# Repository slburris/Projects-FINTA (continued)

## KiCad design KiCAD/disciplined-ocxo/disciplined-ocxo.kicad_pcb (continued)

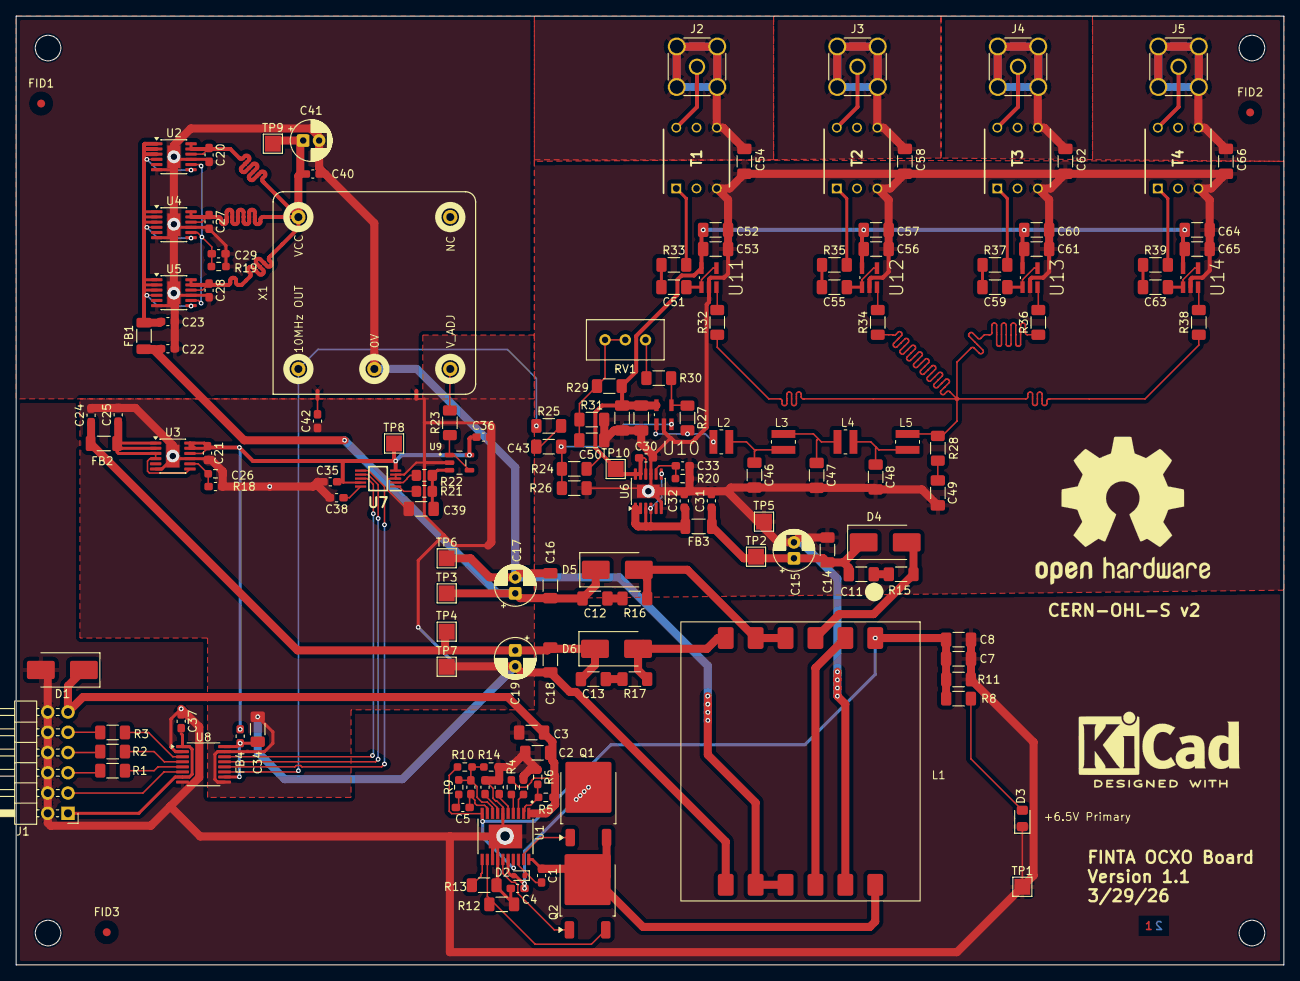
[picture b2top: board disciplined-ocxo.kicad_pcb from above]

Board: 2 copper layers, 159.0 x 119.0 mm, 166 parts (0 on the bottom side), 96 nets.

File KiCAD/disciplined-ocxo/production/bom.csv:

Designator,Footprint,Quantity,Value,LCSC Part #
C1,0603,1,100nf,
C10,0603,1,150pf,
"C11, C12, C13",1206,3,C,
"C14, C16, C18",1206,3,10uf,
"C15, C17, C19, C41",CP_Radial_D5.0mm_P2.00mm,4,100uf polymer,
"C2, C3",1206,2,22uf,
"C20, C21, C22, C23, C24, C25, C27, C28, C30, C31, C32",0603,11,10uf,
"C26, C29, C33",0603,3,4.7uf,
"C34, C39",1206,2,0.22uf,
"C35, C36, C37, C40",0603,4,0.1uf,
C38,0603,1,0.22uf C0G,
C4,0603,1,1uf,
C42,0603,1,0.01uf,
"C43, C45, C53, C57, C61, C65",1206,6,0.001uf C0G,
"C44, C49, C50, C51, C52, C55, C56, C59, C60, C63, C64",1206,11,0.1uf C0G,
"C46, C48",1206,2,390pf C0G,
C47,1206,1,820pf C0G,
C5,0603,1,82pf,
"C54, C58, C62, C66",1206,4,0.01uf,
C6,0603,1,5.1pf,
"C7, C8",1206,2,39uf,
C9,0603,1,33nf,
D1,D_SMB_Handsoldering,1,SMBJ18A,
D2,D_SOD-523,1,"BAS516,115",
D3,0805,1,LED,
"D4, D5, D6",D_SMB_Handsoldering,3,D_Schottky,
"FB1, FB2, FB3",1206,3,BLM31PG601,
FB4,0603,1,BLM18HE152SN1D,
"FID1, FID2, FID3",Fiducial_1mm_Mask3mm,3,Fiducial,
J1,PinHeader_2x06_P2.54mm_Horizontal,1,Conn_02x06_Odd_Even,
"J2, J3, J4, J5",SMA_Amphenol_132291-12_Vertical,4,Conn_Coaxial_Small,
L1,HP6-0090L,1,HP6-0090L,
"L2, L3, L4, L5",IND_VLS3015CX-1R0M-1,4,VLS3015CX-1R0M-1,
"Q1, Q2",TO-252-2,2,GSFD0650,
"R1, R2, R3",1206,3,33,
R10,0603,1,51K,
"R11, R15, R16, R17",1206,4,R,
R12,1206,1,10mohm,
R13,1206,1,10K,
R14,0603,1,12K,
R18,0603,1,49.9K low tc,
R19,0603,1,16.7K low tc,
R20,0603,1,111K low tc,
R21,0805,1,1K 0.01% 5ppm,
R22,0805,1,10K 0.01% 5ppm,
R23,1206,1,100,
"R24, R26",1206,2,47K,
R25,1206,1,1K,
R27,1206,1,2.7K,
"R28, R32, R33, R34, R35, R36, R37, R38, R39",1206,9,49.9,
"R29, R31",1206,2,560,
R30,1206,1,220,
R4,0603,1,1M,
R5,0603,1,15K,
R6,0603,1,2.4K,
R7,0603,1,24K,
R8,1206,1,910,
R9,0603,1,200K,
RV1,Potentiometer_Bourns_3296W_Vertical,1,2.5K,
"T1, T2, T3, T4",DIP762W64P254L826H572Q6N,4,WB1-1L,
"TP1, TP10, TP2, TP3, TP4, TP5, TP6, TP7, TP8, TP9",TestPoint_Pad_2.0x2.0mm,10,TestPoint_Probe,
U1,SOP65P640X110-21N,1,LM25116MHX_NOPB,
"U10, U11, U12, U13, U14",SOT95P290X145-5N,5,AD8055ARTZ-R2,AD8055ARTZ-R2
"U2, U3, U4, U5, U6",MSOP-12-1EP_3x4.039mm_P0.65mm_EP1.651x2.845mm,5,LT3045xMSE,
U7,SOP50P490X110-10N,1,DAC8563SDGSR,
U8,QSOP-16_3.9x4.9mm_P0.635mm,1,Si8641BA-B-IU,
U9,SOT95P280X145-5N,1,OPA192IDBVR,
X1,CTI-OSC-25x25,1,OSC5A2B02,

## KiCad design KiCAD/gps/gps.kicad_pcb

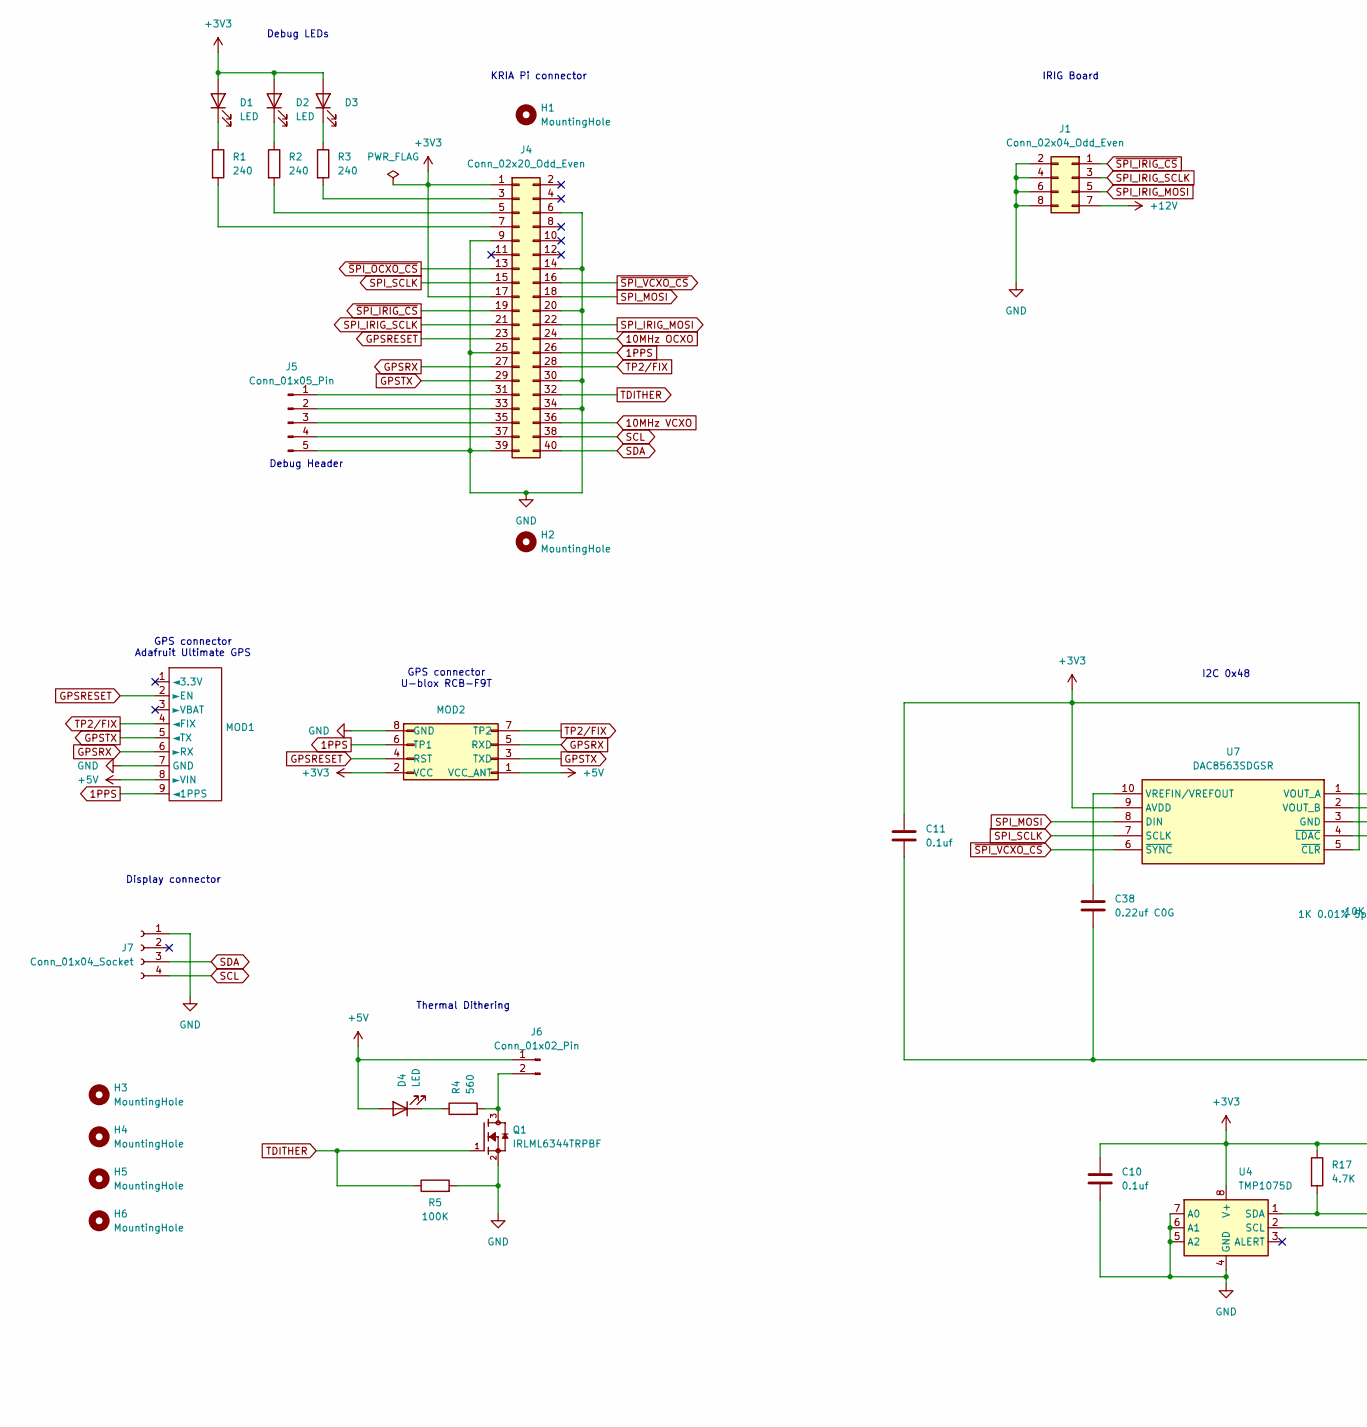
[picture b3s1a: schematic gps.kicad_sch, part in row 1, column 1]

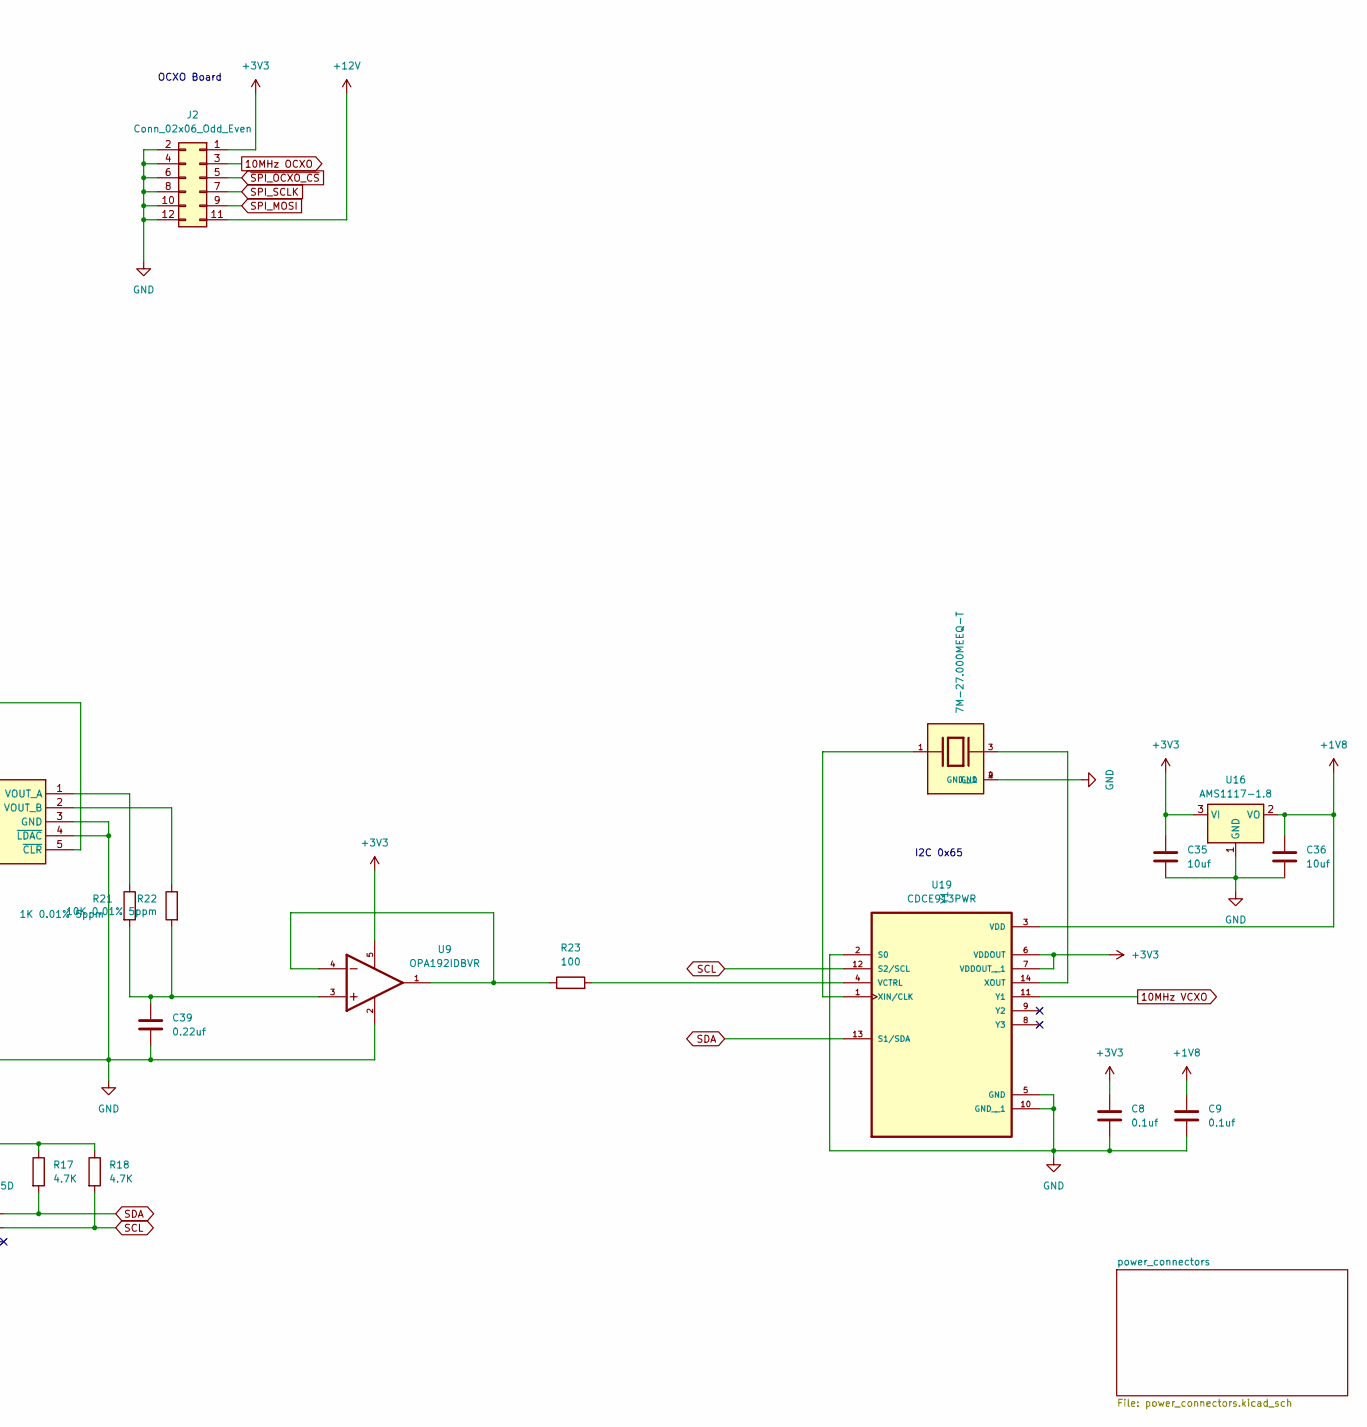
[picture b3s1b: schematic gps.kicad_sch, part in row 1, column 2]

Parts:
C8, C9, C10: 0.1uf; C_0603_1608Metric_Pad1.08x0.95mm_HandSolder
C11: 0.1uf; C_1206_3216Metric_Pad1.33x1.80mm_HandSolder
C35, C36: 10uf; C_1206_3216Metric_Pad1.33x1.80mm_HandSolder
C38: 0.22uf C0G; C_0603_1608Metric_Pad1.08x0.95mm_HandSolder
C39: 0.22uf; C_1206_3216Metric_Pad1.33x1.80mm_HandSolder
D1, D2, D3, D4: LED; LED_0805_2012Metric_Pad1.15x1.40mm_HandSolder
H1, H2: MountingHole; MountingHole_3mm
H3, H4, H5, H6: MountingHole; MountingHole_3.2mm_M3
J1: Conn_02x04_Odd_Even; PinSocket_2x04_P2.54mm_Horizontal
J2: Conn_02x06_Odd_Even; PinSocket_2x06_P2.54mm_Horizontal
J4: Conn_02x20_Odd_Even; PinHeader_2x20_P2.54mm_Vertical
J5: Conn_01x05_Pin; PinHeader_1x05_P2.54mm_Vertical
J6: Conn_01x02_Pin; PinHeader_1x02_P2.54mm_Vertical
J7: Conn_01x04_Socket; JST_PH_B4B-PH-K_1x04_P2.00mm_Vertical
MOD1: Adafruit Ultimate GPS Breakout v3
MOD2: Conn_02x04_Odd_Even; RCB-F9T-0
Q1: IRLML6344TRPBF; TRANS_IRLML6344TRPBF; PARTREV December 19, 2014; DigiKey_Part_Number IRLML6344TRPBFCT-ND
R1, R2, R3: 240; R_1206_3216Metric_Pad1.30x1.75mm_HandSolder
R4: 560; R_1206_3216Metric_Pad1.30x1.75mm_HandSolder
R5: 100K; R_1206_3216Metric_Pad1.30x1.75mm_HandSolder
R17, R18: 4.7K; R_1206_3216Metric_Pad1.30x1.75mm_HandSolder
R21: 1K 0.01% 5ppm; R_0805_2012Metric_Pad1.20x1.40mm_HandSolder
R22: 10K 0.01% 5ppm; R_0805_2012Metric_Pad1.20x1.40mm_HandSolder
R23: 100; R_1206_3216Metric_Pad1.30x1.75mm_HandSolder
U4: TMP1075D; SO-8_3.9x4.9mm_P1.27mm
U7: DAC8563SDGSR; SOP50P490X110-10N; Manufacturer_Part_Number DAC8563SDGSR; Mouser Part Number 595-DAC8563SDGSR
U9: OPA192IDBVR; SOT95P280X145-5N; PARTREV F
U16: AMS1117-1.8; SOT-223-3_TabPin2
U19: CDCE913PWR; SOP65P640X120-14N
Y1: 7M-27.000MEEQ-T; XTAL_7M-27.000MEEQ-T; PARTREV N/A

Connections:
1PPS: J4.26, MOD1.9 (◄1PPS), MOD2.6 (TP1)
10MHz OCXO: J2.3, J4.24
10MHz VCXO: J4.36, U19.11 (Y1)
+1V8: C9.1, C36.1, U16.2 (VO), U19.3 (VDD)
+3V3: C8.1, C10.1, C11.1, C35.1, D1.2 (A), D2.2 (A), D3.2 (A), J2.1, J4.1, J4.17, MOD2.2 (VCC), R17.1, R18.1, U4.8 (V+), U7.5 (~CLR), U7.9 (AVDD), U9.5, U16.3 (VI), U19.6 (VDDOUT), U19.7 (VDDOUT__1)
+5V: D4.2 (A), J6.1, MOD1.8 (►VIN), MOD2.1 (VCC_ANT); also elsewhere on the board
+12V: J1.7, J2.11; also elsewhere on the board
GND: C8.2, C9.2, C10.2, C11.2, C35.2, C36.2, C38.2, C39.2, J1.2, J1.4, J1.6, J1.8, J2.2, J2.4, J2.6, J2.8, J2.10, J2.12, J4.6, J4.9, J4.14, J4.20, J4.25, J4.30, J4.34, J4.39, J5.5, J7.1, MOD1.7 (GND), MOD2.8 (GND), Q1.2, R5.2, U4.4 (GND), U4.5 (A2), U4.6 (A1), U4.7 (A0), U7.3 (GND), U7.4 (~LDAC), U9.2, U16.1 (GND), U19.2 (S0), U19.5 (GND), U19.10 (GND__1), Y1.2 (GND), Y1.4 (GND__1); also elsewhere on the board
GPSRESET: J4.23, MOD1.2 (►EN), MOD2.4 (RST)
GPSRX: J4.27, MOD1.6 (►RX), MOD2.5 (RXD)
GPSTX: J4.29, MOD1.5 (◄TX), MOD2.3 (TXD)
unnamed: C39.1, R21.2, R22.2, U9.3
unnamed: D1.1 (K), R1.1
unnamed: D2.1 (K), R2.1
unnamed: D3.1 (K), R3.1
unnamed: D4.1 (K), R4.1
unnamed: J4.3, R3.2
unnamed: J4.5, R2.2
unnamed: J4.7, R1.2
unnamed: J4.31, J5.1
unnamed: J4.33, J5.2
unnamed: J4.35, J5.3
unnamed: J4.37, J5.4
unnamed: J6.2, Q1.3, R4.2
unnamed: R23.1, U9.1, U9.4
unnamed: R21.1, U7.1 (VOUT_A)
unnamed: R22.1, U7.2 (VOUT_B)
unnamed: C38.1, U7.10 (VREFIN/VREFOUT)
unnamed: R23.2, U19.4 (VCTRL)
unnamed: U19.1 (XIN/CLK), Y1.1
unnamed: U19.14 (XOUT), Y1.3
SCL: J4.38, J7.4, R18.2, U4.2 (SCL), U19.12 (S2/SCL)
SDA: J4.40, J7.3, R17.2, U4.1 (SDA), U19.13 (S1/SDA)
SPI_IRIG_MOSI: J1.5, J4.22
SPI_IRIG_SCLK: J1.3, J4.21
SPI_MOSI: J2.9, J4.18, U7.8 (DIN)
SPI_SCLK: J2.7, J4.15, U7.7 (SCLK)
TDITHER: J4.32, Q1.1, R5.1
TP2/FIX: J4.28, MOD1.4 (◄FIX), MOD2.7 (TP2)
~SPI_IRIG_CS: J1.1, J4.19
~SPI_OCXO_CS: J2.5, J4.13
~SPI_VCXO_CS: J4.16, U7.6 (~SYNC)

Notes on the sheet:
I2C 0x65
I2C 0x48
IRIG Board
Display connector
GPS connector U-blox RCB-F9T
GPS connector Adafruit Ultimate GPS
Debug Header
OCXO Board
Debug LEDs
KRIA Pi connector
Thermal Dithering

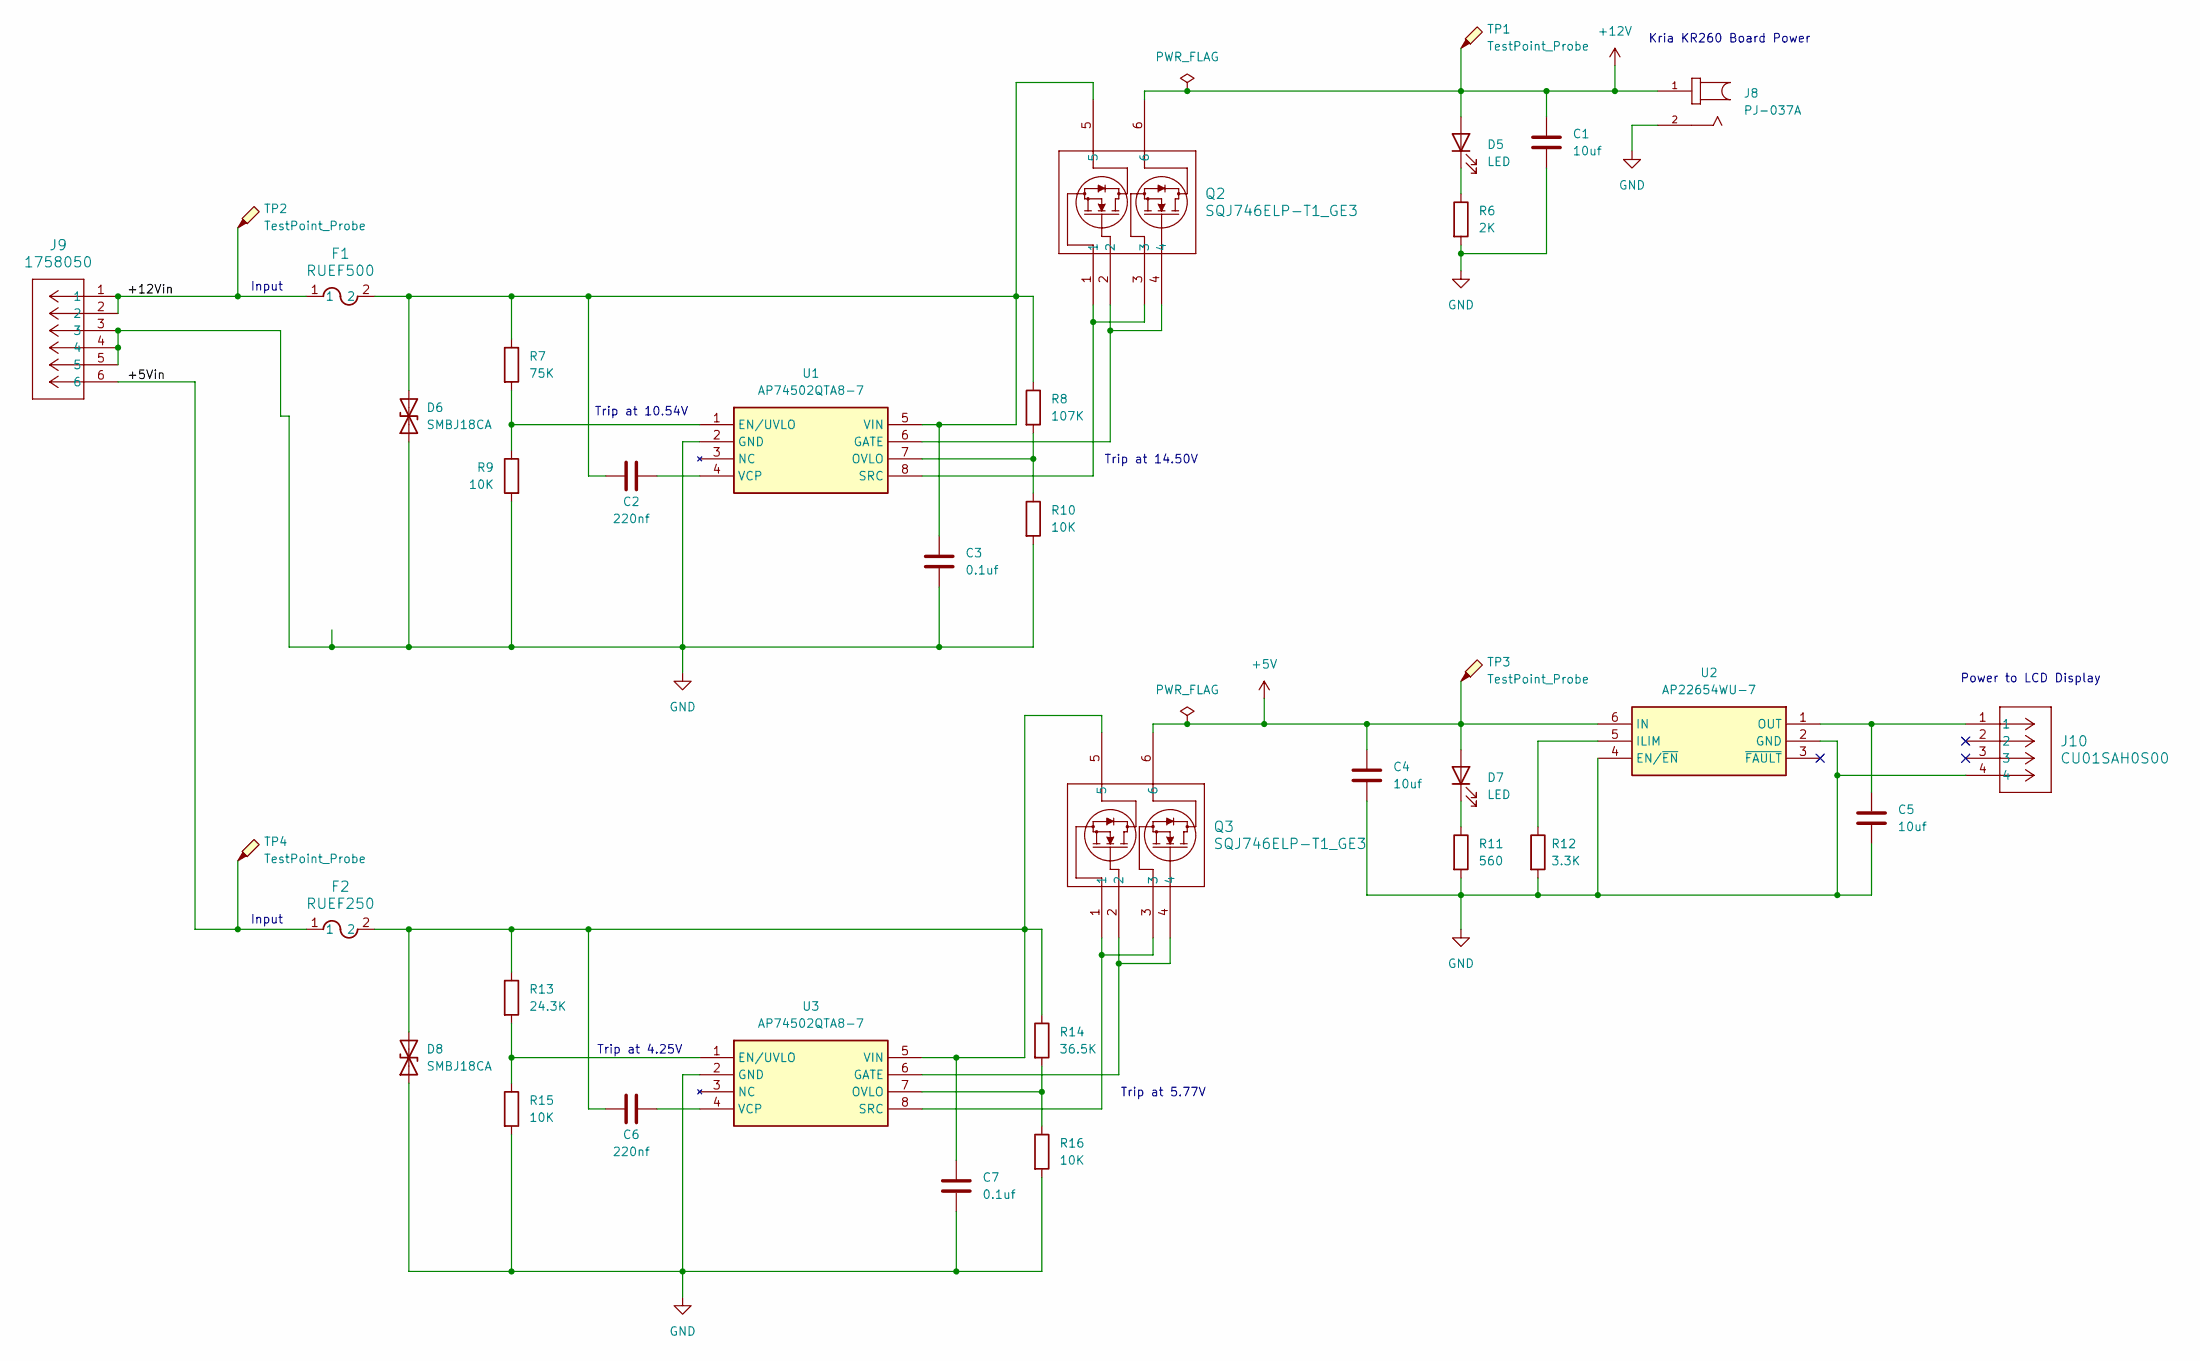
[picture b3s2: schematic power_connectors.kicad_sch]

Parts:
C1, C4, C5: 10uf; C_1206_3216Metric_Pad1.33x1.80mm_HandSolder
C2, C6: 220nf; C_1206_3216Metric_Pad1.33x1.80mm_HandSolder
C3, C7: 0.1uf; C_1206_3216Metric_Pad1.33x1.80mm_HandSolder
D5, D7: LED; LED_0805_2012Metric_Pad1.15x1.40mm_HandSolder
D6, D8: SMBJ18CA; D_SMB_Handsoldering
F1: RUEF500; FUSE_RUEF500_LTF
F2: RUEF250; FUS_RUEF250_TYCO_TYC
J8: PJ-037A; CUI_PJ-037A
J9: 1758050; CONN_1758050
J10: CU01SAH0S00; CONN_CU01SAH0S00_CVI
Q2, Q3: SQJ746ELP-T1_GE3; PowerPAK_SO-8L-2_DUAL_VIS
R6: 2K; R_1206_3216Metric_Pad1.30x1.75mm_HandSolder
R7: 75K; R_1206_3216Metric_Pad1.30x1.75mm_HandSolder
R8: 107K; R_1206_3216Metric_Pad1.30x1.75mm_HandSolder
R9, R10, R15, R16: 10K; R_1206_3216Metric_Pad1.30x1.75mm_HandSolder
R11: 560; R_1206_3216Metric_Pad1.30x1.75mm_HandSolder
R12: 3.3K; R_1206_3216Metric_Pad1.30x1.75mm_HandSolder
R13: 24.3K; R_1206_3216Metric_Pad1.30x1.75mm_HandSolder
R14: 36.5K; R_1206_3216Metric_Pad1.30x1.75mm_HandSolder
TP1, TP2, TP3, TP4: TestPoint_Probe; TestPoint_Pad_2.0x2.0mm
U1, U3: AP74502QTA8-7; SOT65P280X110-8N; Manufacturer_Part_Number AP74502QTA8-7
U2: AP22654WU-7; SOT95P280X82-6N; Mouser Part Number 621-AP22654QWU-7

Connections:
+5V: C4.1, D7.2 (A), Q3.6, TP3.1, U2.6 (IN); also elsewhere on the board
+12V: C1.1, D5.2 (A), J8.1, Q2.6, TP1.1; also elsewhere on the board
/power_connectors/+5Vin: F2.1, J9.6, TP4.1
/power_connectors/+12Vin: F1.1, J9.1, J9.2, TP2.1
GND: C1.2, C3.2, C4.2, C5.2, C7.2, D6.1 (A1), D8.1 (A1), J8.2, J9.3, J9.4, J9.5, J10.4, R6.2, R9.2, R10.2, R11.2, R12.2, R15.2, R16.2, U1.2 (GND), U2.2 (GND), U2.4 (EN/~EN), U3.2 (GND); also elsewhere on the board
unnamed: D5.1 (K), R6.1
unnamed: C2.1, C3.1, D6.2 (A2), F1.2, Q2.5, R7.1, R8.1, U1.5 (VIN)
unnamed: D7.1 (K), R11.1
unnamed: C6.1, C7.1, D8.2 (A2), F2.2, Q3.5, R13.1, R14.1, U3.5 (VIN)
unnamed: R7.2, R9.1, U1.1 (EN/UVLO)
unnamed: Q2.2, Q2.4, U1.6 (GATE)
unnamed: R8.2, R10.1, U1.7 (OVLO)
unnamed: Q2.1, Q2.3, U1.8 (SRC)
unnamed: C2.2, U1.4 (VCP)
unnamed: R12.1, U2.5 (ILIM)
unnamed: C5.1, J10.1, U2.1 (OUT)
unnamed: R13.2, R15.1, U3.1 (EN/UVLO)
unnamed: Q3.2, Q3.4, U3.6 (GATE)
unnamed: R14.2, R16.1, U3.7 (OVLO)
unnamed: Q3.1, Q3.3, U3.8 (SRC)
unnamed: C6.2, U3.4 (VCP)

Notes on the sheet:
Trip at 5.77V
Power to LCD Display
Trip at 10.54V
Trip at 4.25V
Input
Kria KR260 Board Power
Trip at 14.50V

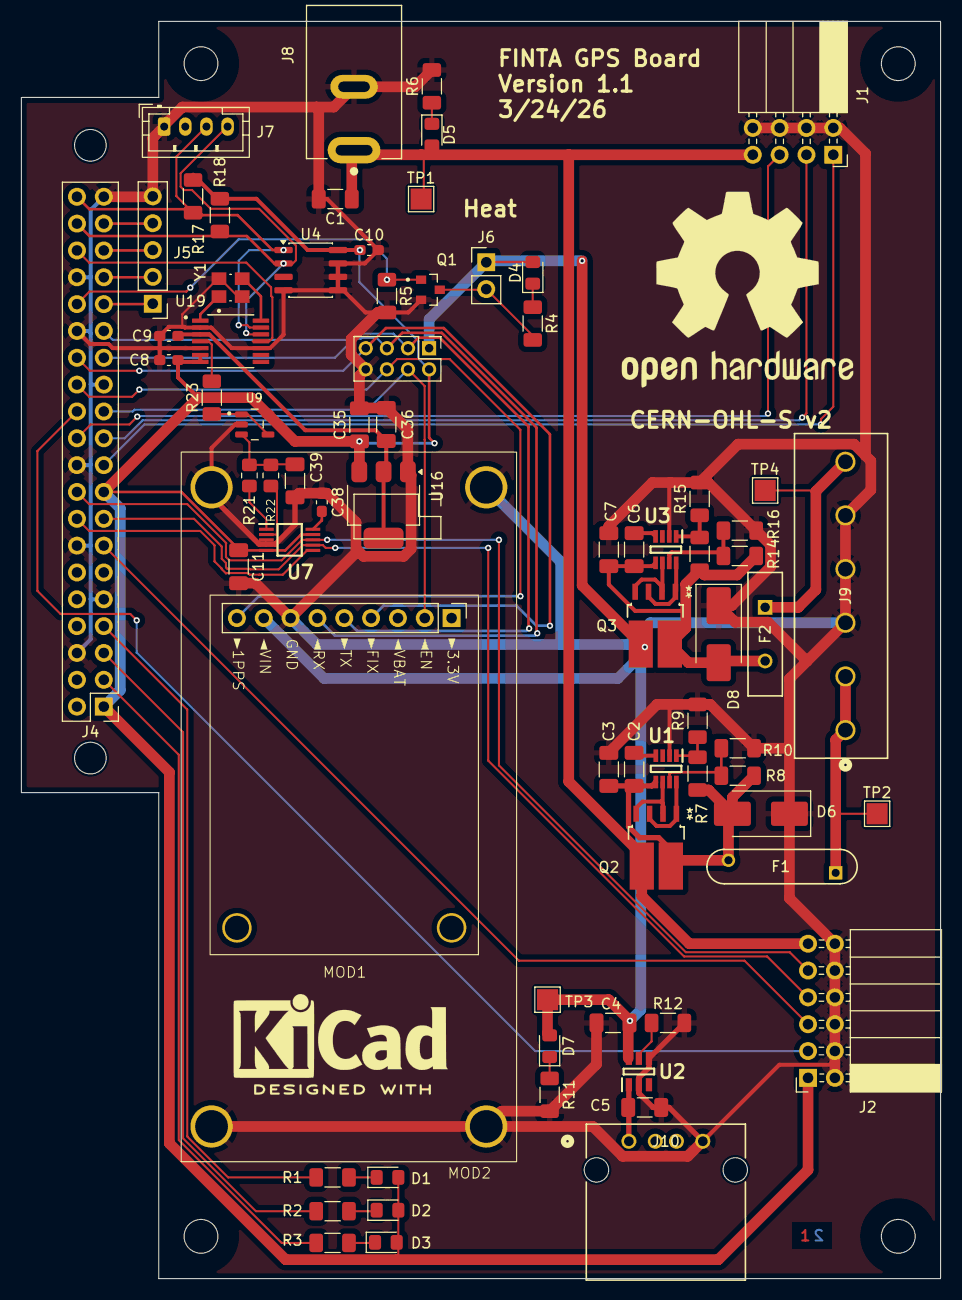
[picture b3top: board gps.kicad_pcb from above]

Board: 2 copper layers, 87.0 x 119.0 mm, 79 parts (0 on the bottom side), 60 nets.

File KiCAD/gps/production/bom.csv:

Designator,Footprint,Quantity,Value,LCSC Part #
"C1, C35, C36, C4, C5",1206,5,10uf,
"C10, C8, C9",0603,3,0.1uf,
"C11, C3, C7",1206,3,0.1uf,
"C2, C6",1206,2,220nf,
C38,0603,1,0.22uf C0G,
C39,1206,1,0.22uf,
"D1, D2, D3, D4, D5, D7",0805,6,LED,
"D6, D8",D_SMB_Handsoldering,2,SMBJ18CA,
F1,FUSE_RUEF500_LTF,1,RUEF500,
F2,FUS_RUEF250_TYCO_TYC,1,RUEF250,
J1,PinSocket_2x04_P2.54mm_Horizontal,1,Conn_02x04_Odd_Even,
J10,CONN_CU01SAH0S00_CVI,1,CU01SAH0S00,
J2,PinSocket_2x06_P2.54mm_Horizontal,1,Conn_02x06_Odd_Even,
J4,PinHeader_2x20_P2.54mm_Vertical,1,Conn_02x20_Odd_Even,
J5,PinHeader_1x05_P2.54mm_Vertical,1,Conn_01x05_Pin,
J6,PinHeader_1x02_P2.54mm_Vertical,1,Conn_01x02_Pin,
J7,JST_PH_B4B-PH-K_1x04_P2.00mm_Vertical,1,Conn_01x04_Socket,
J8,CUI_PJ-037A,1,PJ-037A,
J9,CONN_1758050,1,1758050,
MOD1,Adafruit Ultimate GPS Breakout v3,1,~,
MOD2,RCB-F9T-0,1,Conn_02x04_Odd_Even,
Q1,TRANS_IRLML6344TRPBF,1,IRLML6344TRPBF,
"Q2, Q3",PowerPAK_SO-8L-2_DUAL_VIS,2,SQJ746ELP-T1_GE3,
"R1, R2, R3",1206,3,240,
"R10, R15, R16, R9",1206,4,10K,
"R11, R4",1206,2,560,
R12,1206,1,3.3K,
R13,1206,1,24.3K,
R14,1206,1,36.5K,
"R17, R18",1206,2,4.7K,
R21,0805,1,1K 0.01% 5ppm,
R22,0805,1,10K 0.01% 5ppm,
R23,1206,1,100,
R5,1206,1,100K,
R6,1206,1,2K,
R7,1206,1,75K,
R8,1206,1,107K,
"TP1, TP2, TP3, TP4",TestPoint_Pad_2.0x2.0mm,4,TestPoint_Probe,
"U1, U3",SOT65P280X110-8N,2,AP74502QTA8-7,
U16,SOT-223-3_TabPin2,1,AMS1117-1.8,
U19,SOP65P640X120-14N,1,CDCE913PWR,
U2,SOT95P280X82-6N,1,AP22654WU-7,
U4,SO-8_3.9x4.9mm_P1.27mm,1,TMP1075D,
U7,SOP50P490X110-10N,1,DAC8563SDGSR,
U9,SOT95P280X145-5N,1,OPA192IDBVR,
Y1,XTAL_7M-27.000MEEQ-T,1,7M-27.000MEEQ-T,

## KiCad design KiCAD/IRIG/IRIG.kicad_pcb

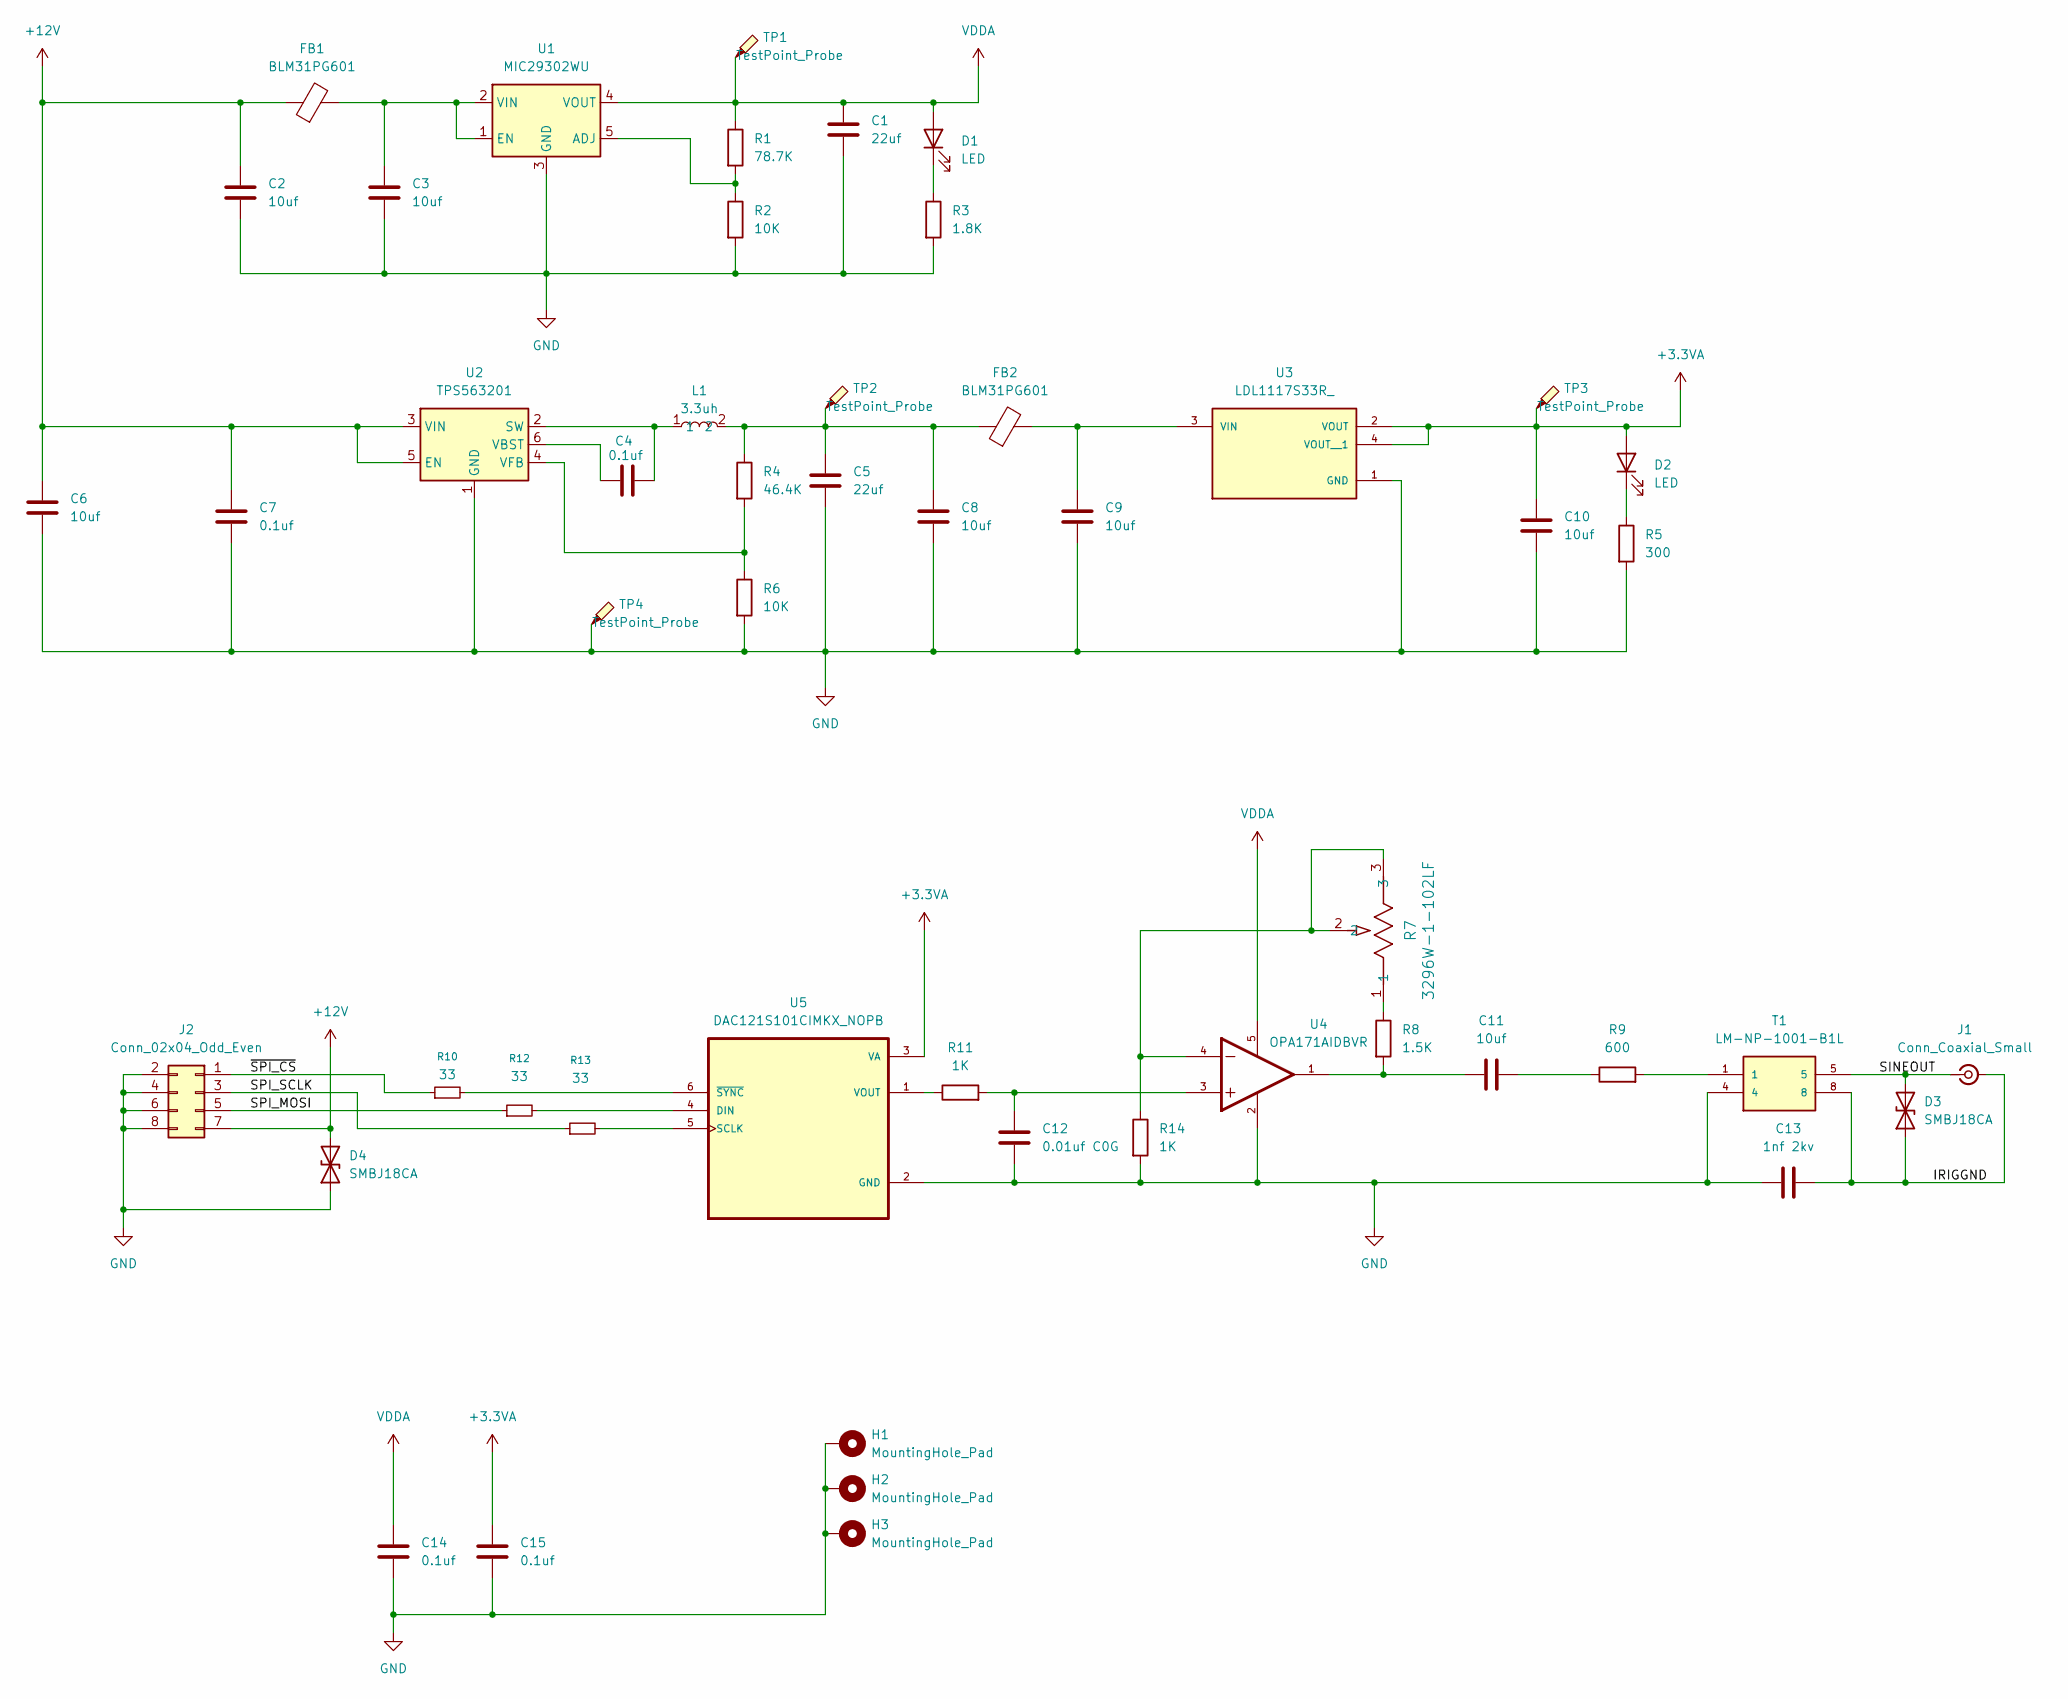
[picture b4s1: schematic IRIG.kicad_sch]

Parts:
C1, C5: 22uf; C_1206_3216Metric_Pad1.33x1.80mm_HandSolder
C2, C3, C6, C8, C9, C10, C11: 10uf; C_1206_3216Metric_Pad1.33x1.80mm_HandSolder
C4, C7, C14, C15: 0.1uf; C_1206_3216Metric_Pad1.33x1.80mm_HandSolder
C12: 0.01uf C0G; C_1206_3216Metric_Pad1.33x1.80mm_HandSolder
C13: 1nf 2kv; C_1206_3216Metric_Pad1.33x1.80mm_HandSolder
D1, D2: LED; LED_0805_2012Metric_Pad1.15x1.40mm_HandSolder
D3, D4: SMBJ18CA; D_SMB_Handsoldering
FB1, FB2: BLM31PG601; L_1206_3216Metric_Pad1.22x1.90mm_HandSolder
H1, H2, H3: MountingHole_Pad; MountingHole_3.2mm_M3_Pad
J1: Conn_Coaxial_Small; SMA_Amphenol_132291-12_Vertical
J2: Conn_02x04_Odd_Even; PinHeader_2x04_P2.54mm_Horizontal
L1: 3.3uh; BCIHP10SC
R1: 78.7K; R_1206_3216Metric_Pad1.30x1.75mm_HandSolder
R2, R6: 10K; R_1206_3216Metric_Pad1.30x1.75mm_HandSolder
R3: 1.8K; R_1206_3216Metric_Pad1.30x1.75mm_HandSolder
R4: 46.4K; R_1206_3216Metric_Pad1.30x1.75mm_HandSolder
R5: 300; R_1206_3216Metric_Pad1.30x1.75mm_HandSolder
R7: 3296W-1-102LF; POT_3296W
R8: 1.5K; R_1206_3216Metric_Pad1.30x1.75mm_HandSolder
R9: 600; R_1206_3216Metric_Pad1.30x1.75mm_HandSolder
R10, R12, R13: 33; R_1206_3216Metric_Pad1.30x1.75mm_HandSolder
R11, R14: 1K; R_1206_3216Metric_Pad1.30x1.75mm_HandSolder
T1: LM-NP-1001-B1L; LMNP1001B1L; MOUSER_PART_NUMBER 652-LM-NP-1001-B1L; DigiKey_Part_Number LM-NP-1001-B1L-ND
TP1, TP2, TP3, TP4: TestPoint_Probe; TestPoint_Pad_2.0x2.0mm
U1: MIC29302WU; TO-263-5_TabPin3
U2: TPS563201; SOT-23-6
U3: LDL1117S33R_; SOT230P700X180-4N; PARTREV 7
U4: OPA171AIDBVR; SOT95P280X145-5NOPA171
U5: DAC121S101CIMKX_NOPB; SOT95P280X110-6N

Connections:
+3.3VA: C10.1, C15.1, D2.2 (A), TP3.1, U3.2 (VOUT), U3.4 (VOUT__1), U5.3 (VA)
+12V: C2.1, C6.1, C7.1, D4.2 (A2), FB1.1, J2.7, U2.3 (VIN), U2.5 (EN)
/IRIGGND: C13.2, D3.1 (A1), J1.2 (Ext), T1.8
/SINEOUT: D3.2 (A2), J1.1 (In), T1.5
/SPI_MOSI: J2.5, R12.1
/SPI_SCLK: J2.3, R13.1
/~SPI_CS: J2.1, R10.1
GND: C1.2, C2.2, C3.2, C5.2, C6.2, C7.2, C8.2, C9.2, C10.2, C12.2, C13.1, C14.2, C15.2, D4.1 (A1), H1.1, H2.1, H3.1, J2.2, J2.4, J2.6, J2.8, R2.2, R3.2, R5.2, R6.2, R14.2, T1.4, TP4.1, U1.3 (GND), U2.1 (GND), U3.1 (GND), U4.2, U5.2 (GND)
unnamed: C5.1, C8.1, FB2.1, L1.2, R4.1, TP2.1
unnamed: C11.1, R8.2, U4.1
unnamed: C11.2, R9.1
unnamed: C12.1, R11.2, U4.3
unnamed: D1.1 (K), R3.1
unnamed: D2.1 (K), R5.1
unnamed: R7.1, R8.1
unnamed: R9.2, T1.1
unnamed: R7.2, R7.3, R14.1, U4.4
unnamed: R1.2, R2.1, U1.5 (ADJ)
unnamed: C3.1, FB1.2, U1.1 (EN), U1.2 (VIN)
unnamed: C4.2, L1.1, U2.2 (SW)
unnamed: C4.1, U2.6 (VBST)
unnamed: R4.2, R6.1, U2.4 (VFB)
unnamed: C9.1, FB2.2, U3.3 (VIN)
unnamed: R12.2, U5.4 (DIN)
unnamed: R13.2, U5.5 (SCLK)
unnamed: R11.1, U5.1 (VOUT)
unnamed: R10.2, U5.6 (~SYNC)
VDDA: C1.1, C14.1, D1.2 (A), R1.1, TP1.1, U1.4 (VOUT), U4.5

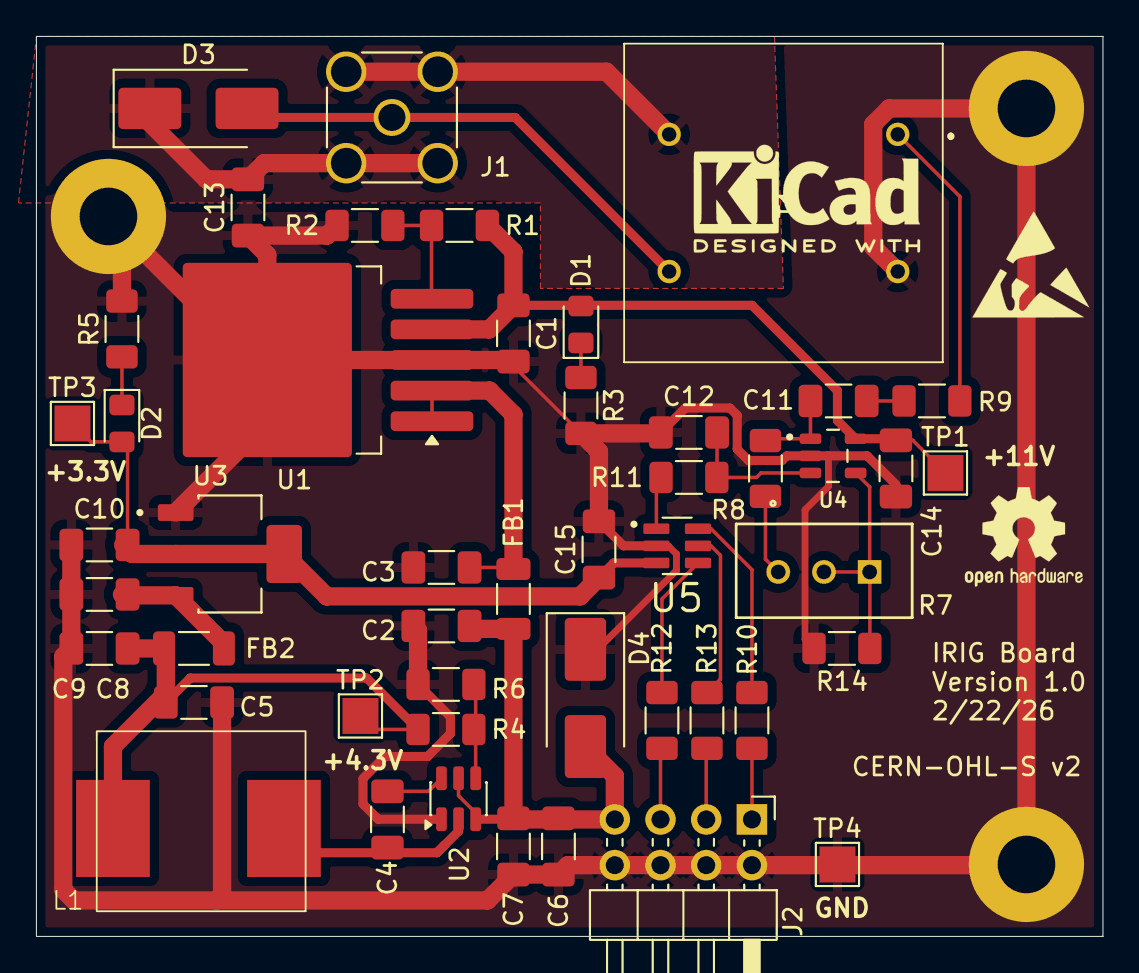
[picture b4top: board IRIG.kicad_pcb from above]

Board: 2 copper layers, 59.2 x 50.0 mm, 51 parts (0 on the bottom side), 28 nets.

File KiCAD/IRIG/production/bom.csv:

Designator,Footprint,Quantity,Value,LCSC Part #
"C1, C5",1206,2,22uf,
"C10, C11, C2, C3, C6, C8, C9",1206,7,10uf,
C12,1206,1,0.01uf C0G,
C13,1206,1,1nf 2kv,
"C14, C15, C4, C7",1206,4,0.1uf,
"D1, D2",0805,2,LED,
"D3, D4",D_SMB_Handsoldering,2,SMBJ18CA,
"FB1, FB2",1206,2,BLM31PG601,
J1,SMA_Amphenol_132291-12_Vertical,1,Conn_Coaxial_Small,
J2,PinHeader_2x04_P2.54mm_Horizontal,1,Conn_02x04_Odd_Even,
L1,BCIHP10SC,1,3.3uh,
R1,1206,1,78.7K,
"R10, R12, R13",1206,3,33,
"R11, R14",1206,2,1K,
"R2, R6",1206,2,10K,
R3,1206,1,1.8K,
R4,1206,1,46.4K,
R5,1206,1,300,
R7,POT_3296W,1,3296W-1-102LF,
R8,1206,1,1.5K,
R9,1206,1,600,
T1,LMNP1001B1L,1,LM-NP-1001-B1L,
"TP1, TP2, TP3, TP4",TestPoint_Pad_2.0x2.0mm,4,TestPoint_Probe,
U1,TO-263-5_TabPin3,1,MIC29302WU,
U2,SOT-23-6,1,TPS563201,
U3,SOT230P700X180-4N,1,LDL1117S33R_,
U4,SOT95P280X145-5NOPA171,1,OPA171AIDBVR,
U5,SOT95P280X110-6N,1,DAC121S101CIMKX_NOPB,
